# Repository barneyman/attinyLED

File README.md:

# attinyLED
ws2812B I2C driver using attiny85.

The tiny85 is now an I2C slave that can drive a string of ws2812B leds.

There are two builds - Palette and non-Palette.

The latter will let you control ~90 LEDs, and set RGB for each one, while the former allows you to address ~300 of 
them using a pre-defined palette (basically the web pallete) - there are 8 user palettes available.

There's also a rudimentary macro capability, and it will also run the macro on a PCint.

This project uses my fork of TinyWire (to bubble the PCINT up) - the example app ( https://github.com/barneyman/espMaster )
can be used as a template to drive it - there is a library (ATleds) in https://github.com/barneyman/myLibraries that will 
drive the I2C from a master

The project also includes the eagle and gerber files for the board
The board was produced by ALLPCB for US$15 for 5

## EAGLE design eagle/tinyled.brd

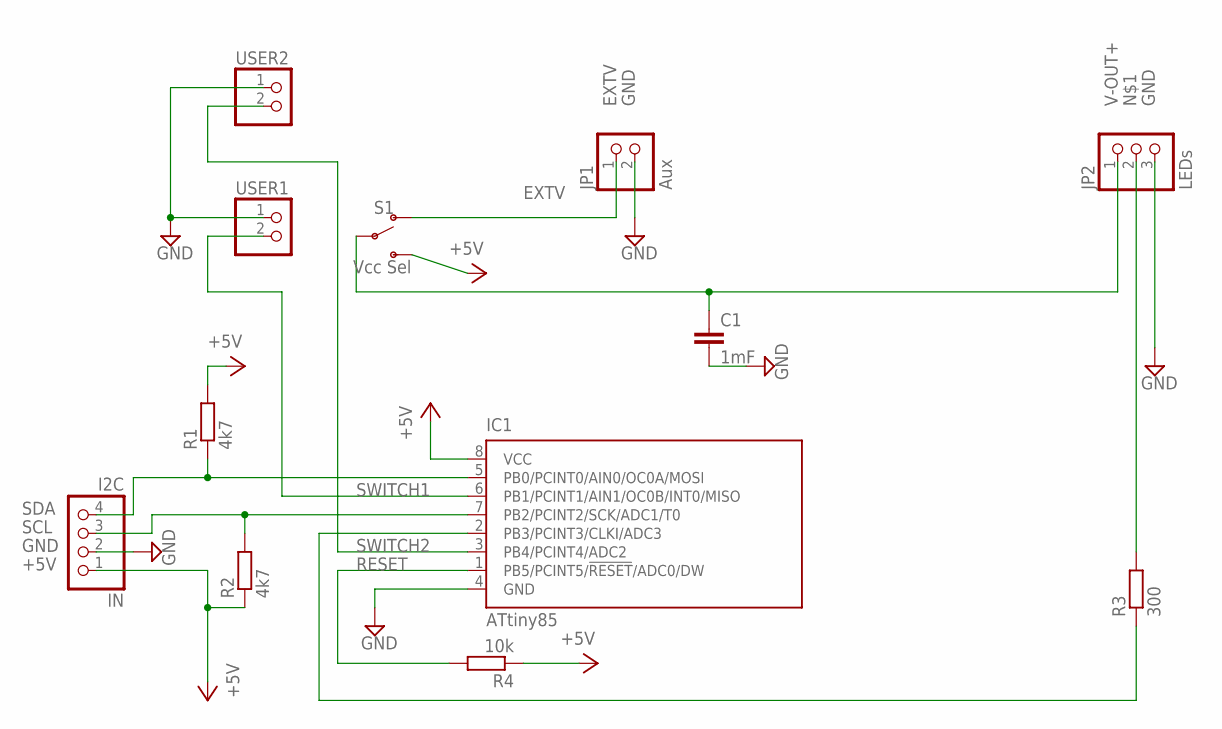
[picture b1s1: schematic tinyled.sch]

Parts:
C1: 1mF; C050-025X075
IC1: ATtiny85; DIL08
IN: I2C; 1X04/90
JP1: Aux; 1X02/90
JP2: LEDs; 1X03/90
R1, R2: 4k7; 0204/7
R3: 300; 0204/7
R4: 10k; 0204/7
S1: Vcc Sel; SWITCH_SPDT_PTH_11.6X4.0MM
USER1, USER2: PINHD-1X2; 1X02

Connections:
+5V: IC1.8 (VCC), IN.1, R1.2, R2.1, R4.1, S1.3 (S)
DATA: IC1.2 (PB3/PCINT3/CLKI/ADC3), R3.1
EXTV: JP1.1, S1.1 (O)
GND: C1.2, IC1.4 (GND), IN.2, JP1.2, JP2.3, USER1.1, USER2.1
unnamed: JP2.2, R3.2
RESET: IC1.1 (PB5/PCINT5/!RESET!/ADC0/DW), R4.2
SCL: IC1.7 (PB2/PCINT2/SCK/ADC1/T0), IN.3, R2.2
SDA: IC1.5 (PB0/PCINT0/AIN0/OC0A/MOSI), IN.4, R1.1
SWITCH1: IC1.6 (PB1/PCINT1/AIN1/OC0B/INT0/MISO), USER1.2
SWITCH2: IC1.3 (PB4/PCINT4/ADC2), USER2.2
V-OUT+: C1.1, JP2.1, S1.2

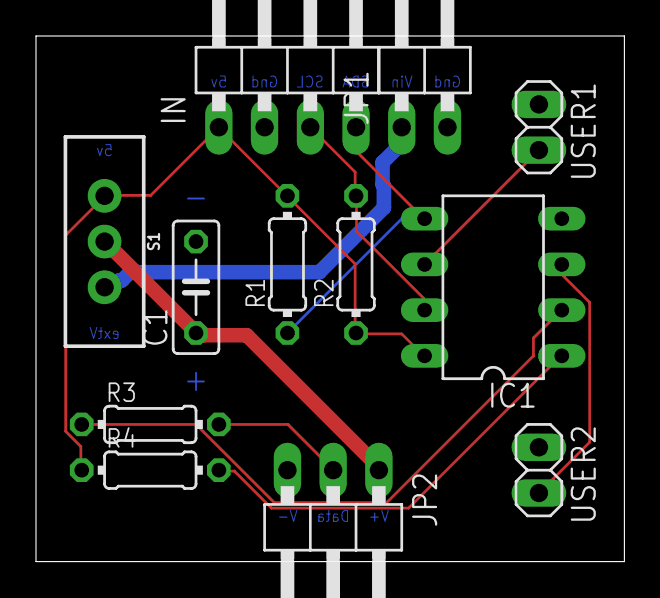
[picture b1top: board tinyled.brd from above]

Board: 2 copper layers, 32.7 x 29.2 mm, 12 parts (0 on the bottom side), 11 nets.

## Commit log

2018-04-19 bounds checking and ignores
2018-04-21 interrupt driven i2c now
2018-04-21 added invert, and mosly working now
2018-04-24 something goes scatty with i2c 100 or so Display requests in
2018-04-28 fixed the random reset - it appears that I2C recv does not guarantee the whole transmission atom, and it can be delivered in multiples - still a crash after a couple of iterations of the test harness
2018-05-02 do the hard work in the ISR
2018-05-06 disabling timer seems to make it more stable - still crashes - excluding ws2821 code currently
2018-05-06 Display asynch now, out of ISR
    Still a blocking crash in the I2C somewhere
2018-05-10 added a palette option
2018-05-11 added a div to the palette, put the palette into progmem
2018-05-11 added user palette display code - chip speed now needs to be 16mhz
2018-05-11 implemented userPalette
2018-05-11 some descriptive prose
2018-05-12 assume progmem, add another circQueue for macros
2018-05-12 macros run now
2018-05-14 handle button push
2018-05-15 handle a button being pressed (after changing twi to pass that pcint up)
2018-05-15 added delay command - i've dramtically reduced LED size - i'm getting stack corruption
2018-05-15 added stack checking, reset MAXLEDS to something more appropriate for each build type
2018-05-16 delay before Display seems to fix the I2C race condition (tested with 200 leds)
2018-05-16 added board
2018-05-16 can't use millis() either side of a cli! So, calculate lag
2018-05-16 roll works now
2018-05-17 fixed shiort circuits in design
2018-05-17 moved circQ to libraries
2018-05-23 added images
2018-05-23 more blurb
2018-05-27 explicit instantiation
2018-07-05 circq has changed
2018-09-09 some cleanup

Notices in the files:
parts and their libraries:
SparkFun-Switches: Licensing: Creative Commons ShareAlike 4.0 International - https://creativecommons.org/licenses/by-sa/4.0
